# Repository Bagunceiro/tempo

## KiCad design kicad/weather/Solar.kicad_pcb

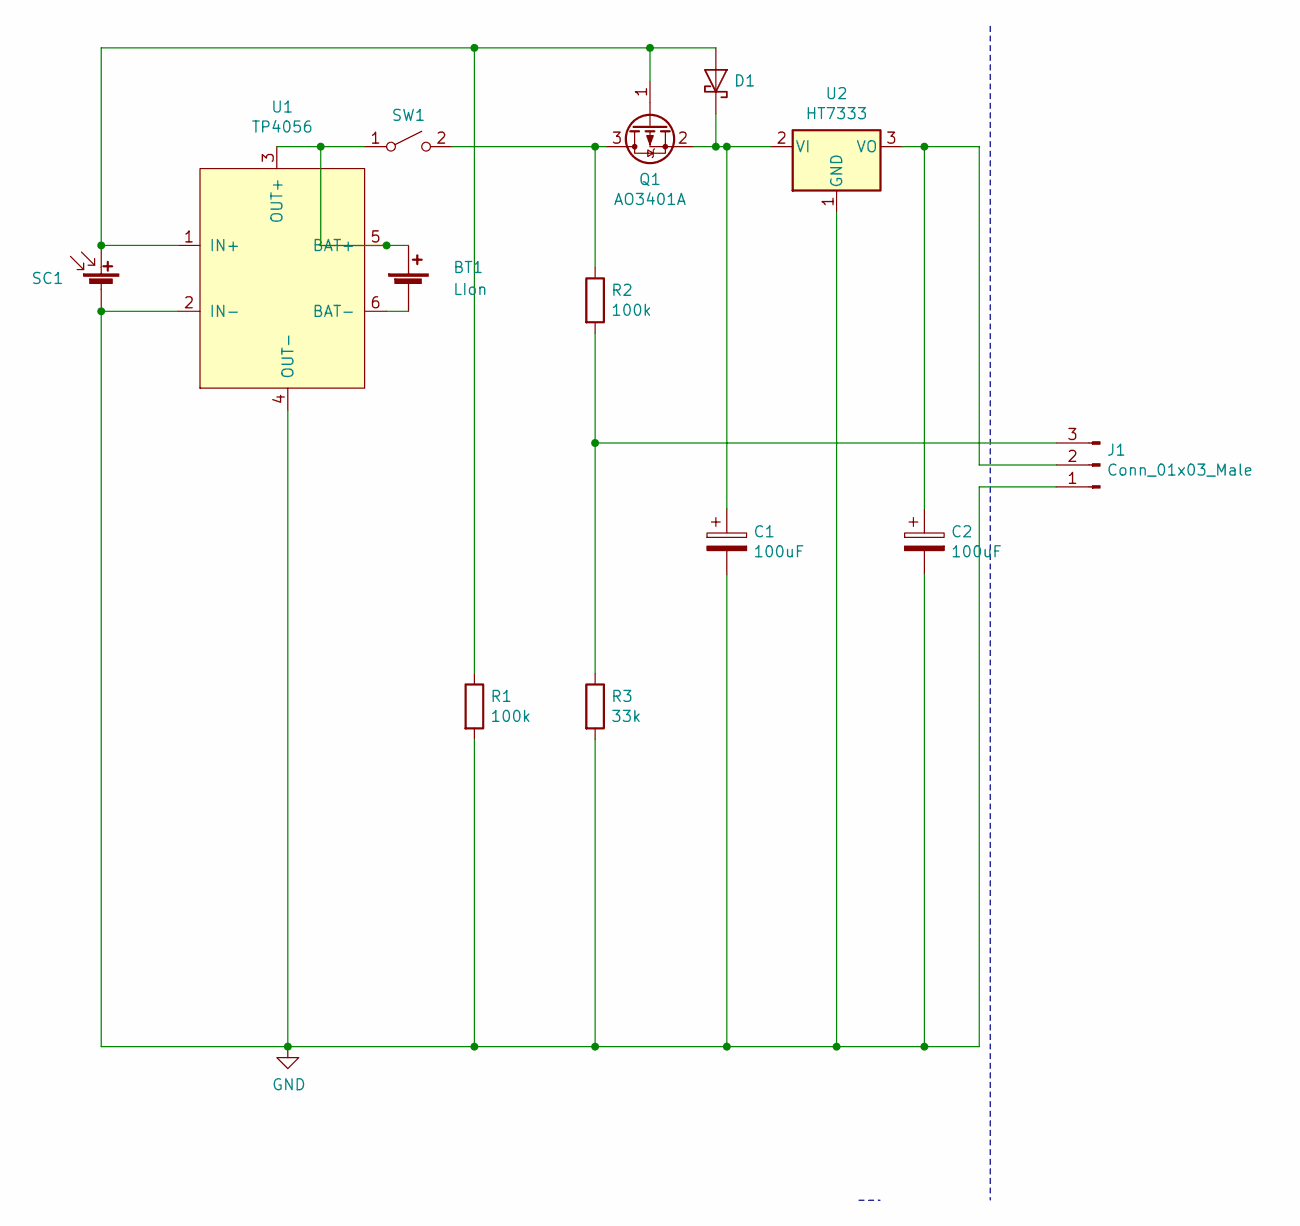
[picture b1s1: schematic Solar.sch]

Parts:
BT1: LIon; Molex_KK-254_AE-6410-02A_1x02_P2.54mm_Vertical
C1, C2: 100uF; C_Radial_D5.0mm_H11.0mm_P2.00mm
D1: D_Schottky; D_A-405_P10.16mm_Horizontal
J1: Conn_01x03_Male; Molex_KK-254_AE-6410-03A_1x03_P2.54mm_Vertical
Q1: AO3401A; TO-220-3_Vertical
R1, R2: 100k; R_Axial_DIN0207_L6.3mm_D2.5mm_P5.08mm_Vertical
R3: 33k; R_Axial_DIN0207_L6.3mm_D2.5mm_P5.08mm_Vertical
SC1: Solar_Cell; Molex_KK-254_AE-6410-02A_1x02_P2.54mm_Vertical
SW1: SW_SPST; PinHeader_1x02_P2.54mm_Vertical
U1: TP4056
U2: HT7333; TO-92_Inline

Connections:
GND: C1.2, C2.2, J1.1, R1.2, R3.2, SC1.2 (-), U1.2 (IN-), U1.4 (OUT-), U2.1 (GND)
unnamed: BT1.1 (+), SW1.1 (A), U1.3 (OUT+), U1.5 (BAT+)
unnamed: BT1.2 (-), U1.6 (BAT-)
unnamed: C1.1, D1.1 (K), Q1.2 (S), U2.2 (VI)
unnamed: C2.1, J1.2, U2.3 (VO)
unnamed: D1.2 (A), Q1.1 (G), R1.1, SC1.1 (+), U1.1 (IN+)
unnamed: J1.3, R2.2, R3.1
unnamed: Q1.3 (D), R2.1, SW1.2 (B)

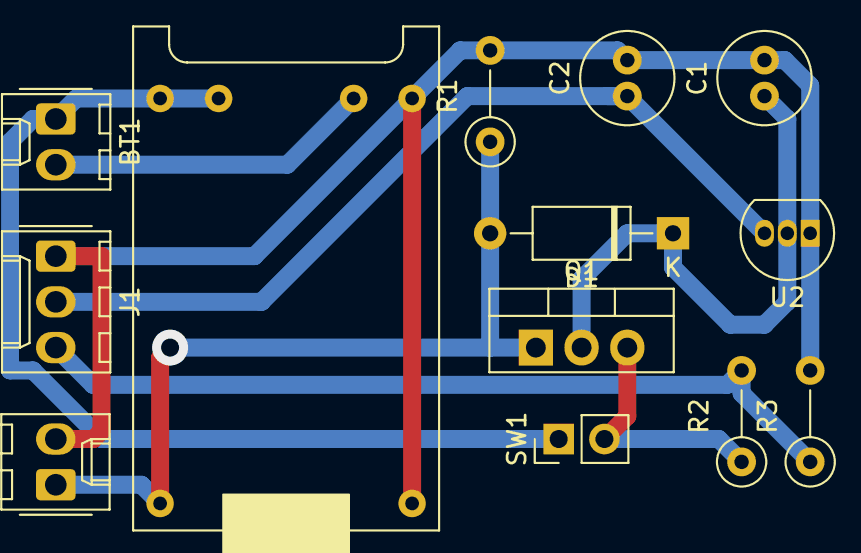
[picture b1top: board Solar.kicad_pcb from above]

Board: 2 copper layers, 13 parts (0 on the bottom side), 8 nets.

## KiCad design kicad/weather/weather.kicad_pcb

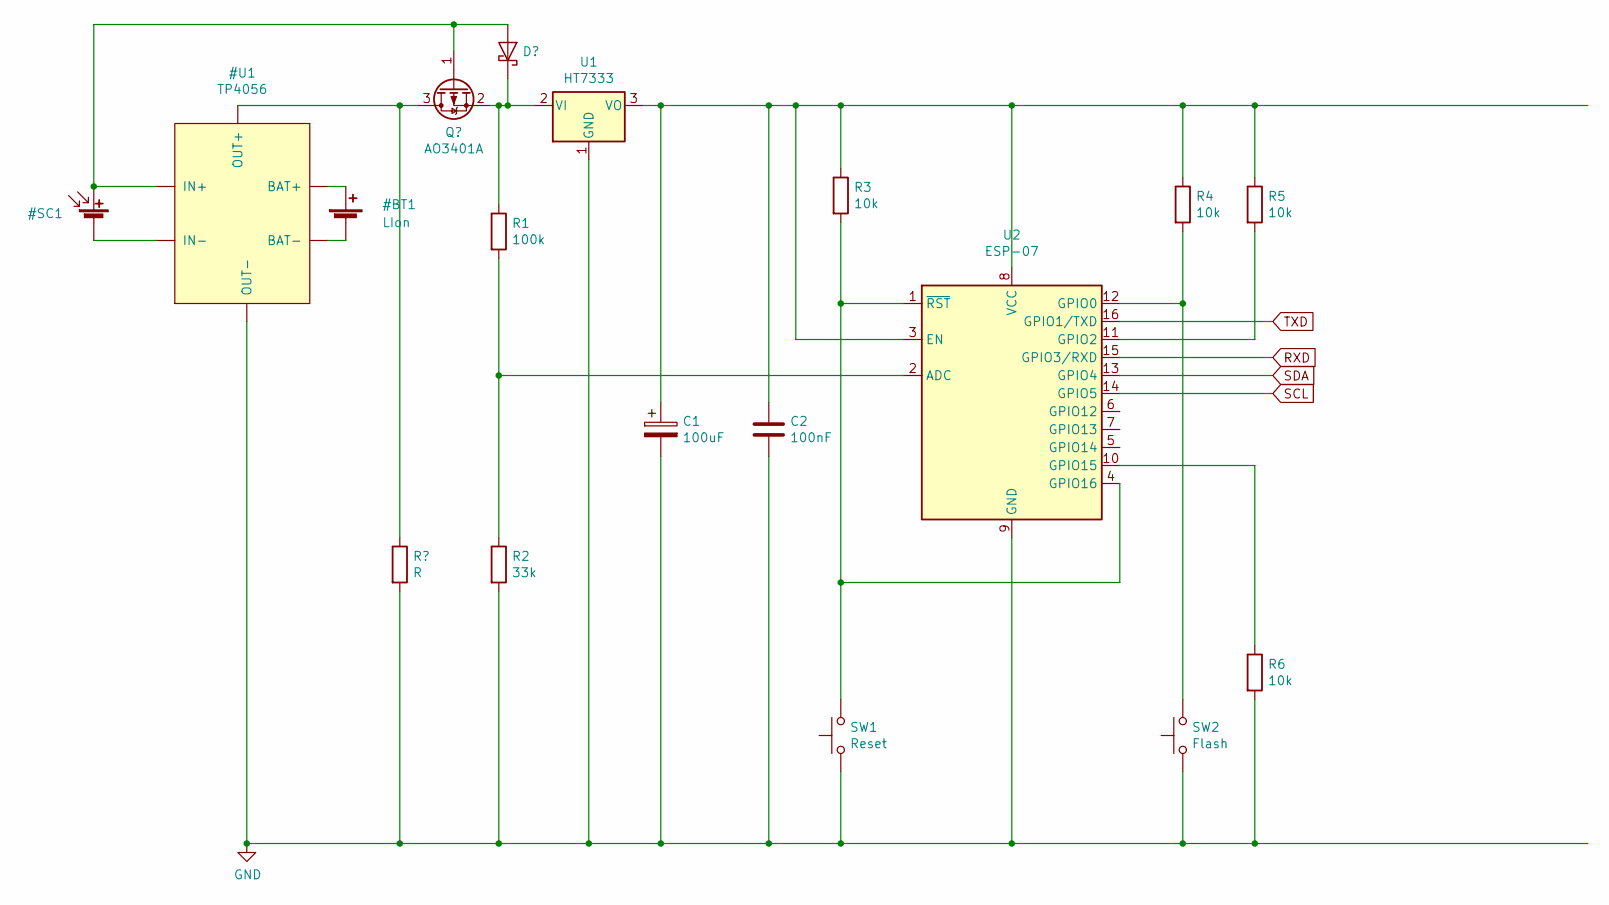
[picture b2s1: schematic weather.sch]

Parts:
C1: 100uF; C_Radial_D5.0mm_H11.0mm_P2.00mm
C2: 100nF; C_0805_2012Metric_Pad1.15x1.40mm_HandSolder
R1: 100k; R_Axial_DIN0207_L6.3mm_D2.5mm_P5.08mm_Vertical
R2: 33k; R_Axial_DIN0207_L6.3mm_D2.5mm_P5.08mm_Vertical
R3, R4, R5, R6: 10k; R_Axial_DIN0207_L6.3mm_D2.5mm_P5.08mm_Vertical
SW1: Reset; SW_PUSH_6mm
SW2: Flash; SW_PUSH_6mm
U1: HT7333; TO-92_Inline
U2: ESP-07

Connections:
unnamed: C1.1, C2.1, R3.1, R4.1, R5.1, U1.3 (VO), U2.3 (EN), U2.8 (VCC)
unnamed 1: C1.2, C2.2, R2.2, R6.2, SW1.1, SW2.1, U1.1 (GND), U2.9 (GND); also elsewhere on the board
unnamed 2: U2.16 (GPIO1/TXD); also elsewhere on the board
unnamed 3: U2.15 (GPIO3/RXD); also elsewhere on the board
unnamed: R1.1, U1.2 (VI)
unnamed: R1.2, R2.1, U2.2 (ADC)
unnamed: R3.2, SW1.2, U2.1 (~RST), U2.4 (GPIO16)
unnamed: R4.2, SW2.2, U2.12 (GPIO0)
unnamed: R5.2, U2.11 (GPIO2)
unnamed: R6.1, U2.10 (GPIO15)
SCL: U2.14 (GPIO5)
SDA: U2.13 (GPIO4)

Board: 2 copper layers, 13 parts (0 on the bottom side), 10 nets, no tracks yet.

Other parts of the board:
J1: Prog; PinHeader_1x03_P2.54mm_Vertical

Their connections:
unnamed 1: J1.3; also elsewhere on the board
unnamed 2: J1.1; also elsewhere on the board
unnamed 3: J1.2; also elsewhere on the board

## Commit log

2020-11-17 initial
2021-05-21 baselining
2022-06-16 Clean up of project structure
2022-06-16 rename
